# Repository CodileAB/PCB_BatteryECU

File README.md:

Wolley Battery ECU
==================

This is the KiCad project for the Wolley Battery ECU.

Specifications
--------------

| Name                       | Value          |
| -------------------------- | -------------- |
| PCB layers                 | 2              |
| PCB width                  | 103.20 mm      |
| PCB height                 | 117.00 mm      |
| Mount hole diameter        | 3.20 mm        |
| Bus voltage                | 5 V            |
| Max current                | 5 A            |
| Number of cells            | 10             |
| Cell type                  | Ni-MH (AA)     |
| Integrated charging        | Yes            |

Key Components
--------------

| Component | Part | Details |
| --------- | ---- | ------- |
| MCU | Infineon XMC1404_F064X200A | ARM Cortex-M0, 32-bit, 48 MHz, 200 kB flash |
| Step-down voltage regulator | TI LM22679TJ-5.0 | 42 V to 5 V switching regulator, 5 A |
| CAN transceiver | Infineon TLE7251VSJ | |
| Current sensor | MPS MCS1803GS-05P | Hall effect current sensor, 5 A |
| Temperature sensor | TI LM35DM | Precision centigrade temperature sensor |
| Battery charger | Maxim MAX1640 | Adjustable-output, switch-mode current sources with synchronous rectifier |

Licence
-------

Licenced under the CERN Open Hardware Licence v1.2.

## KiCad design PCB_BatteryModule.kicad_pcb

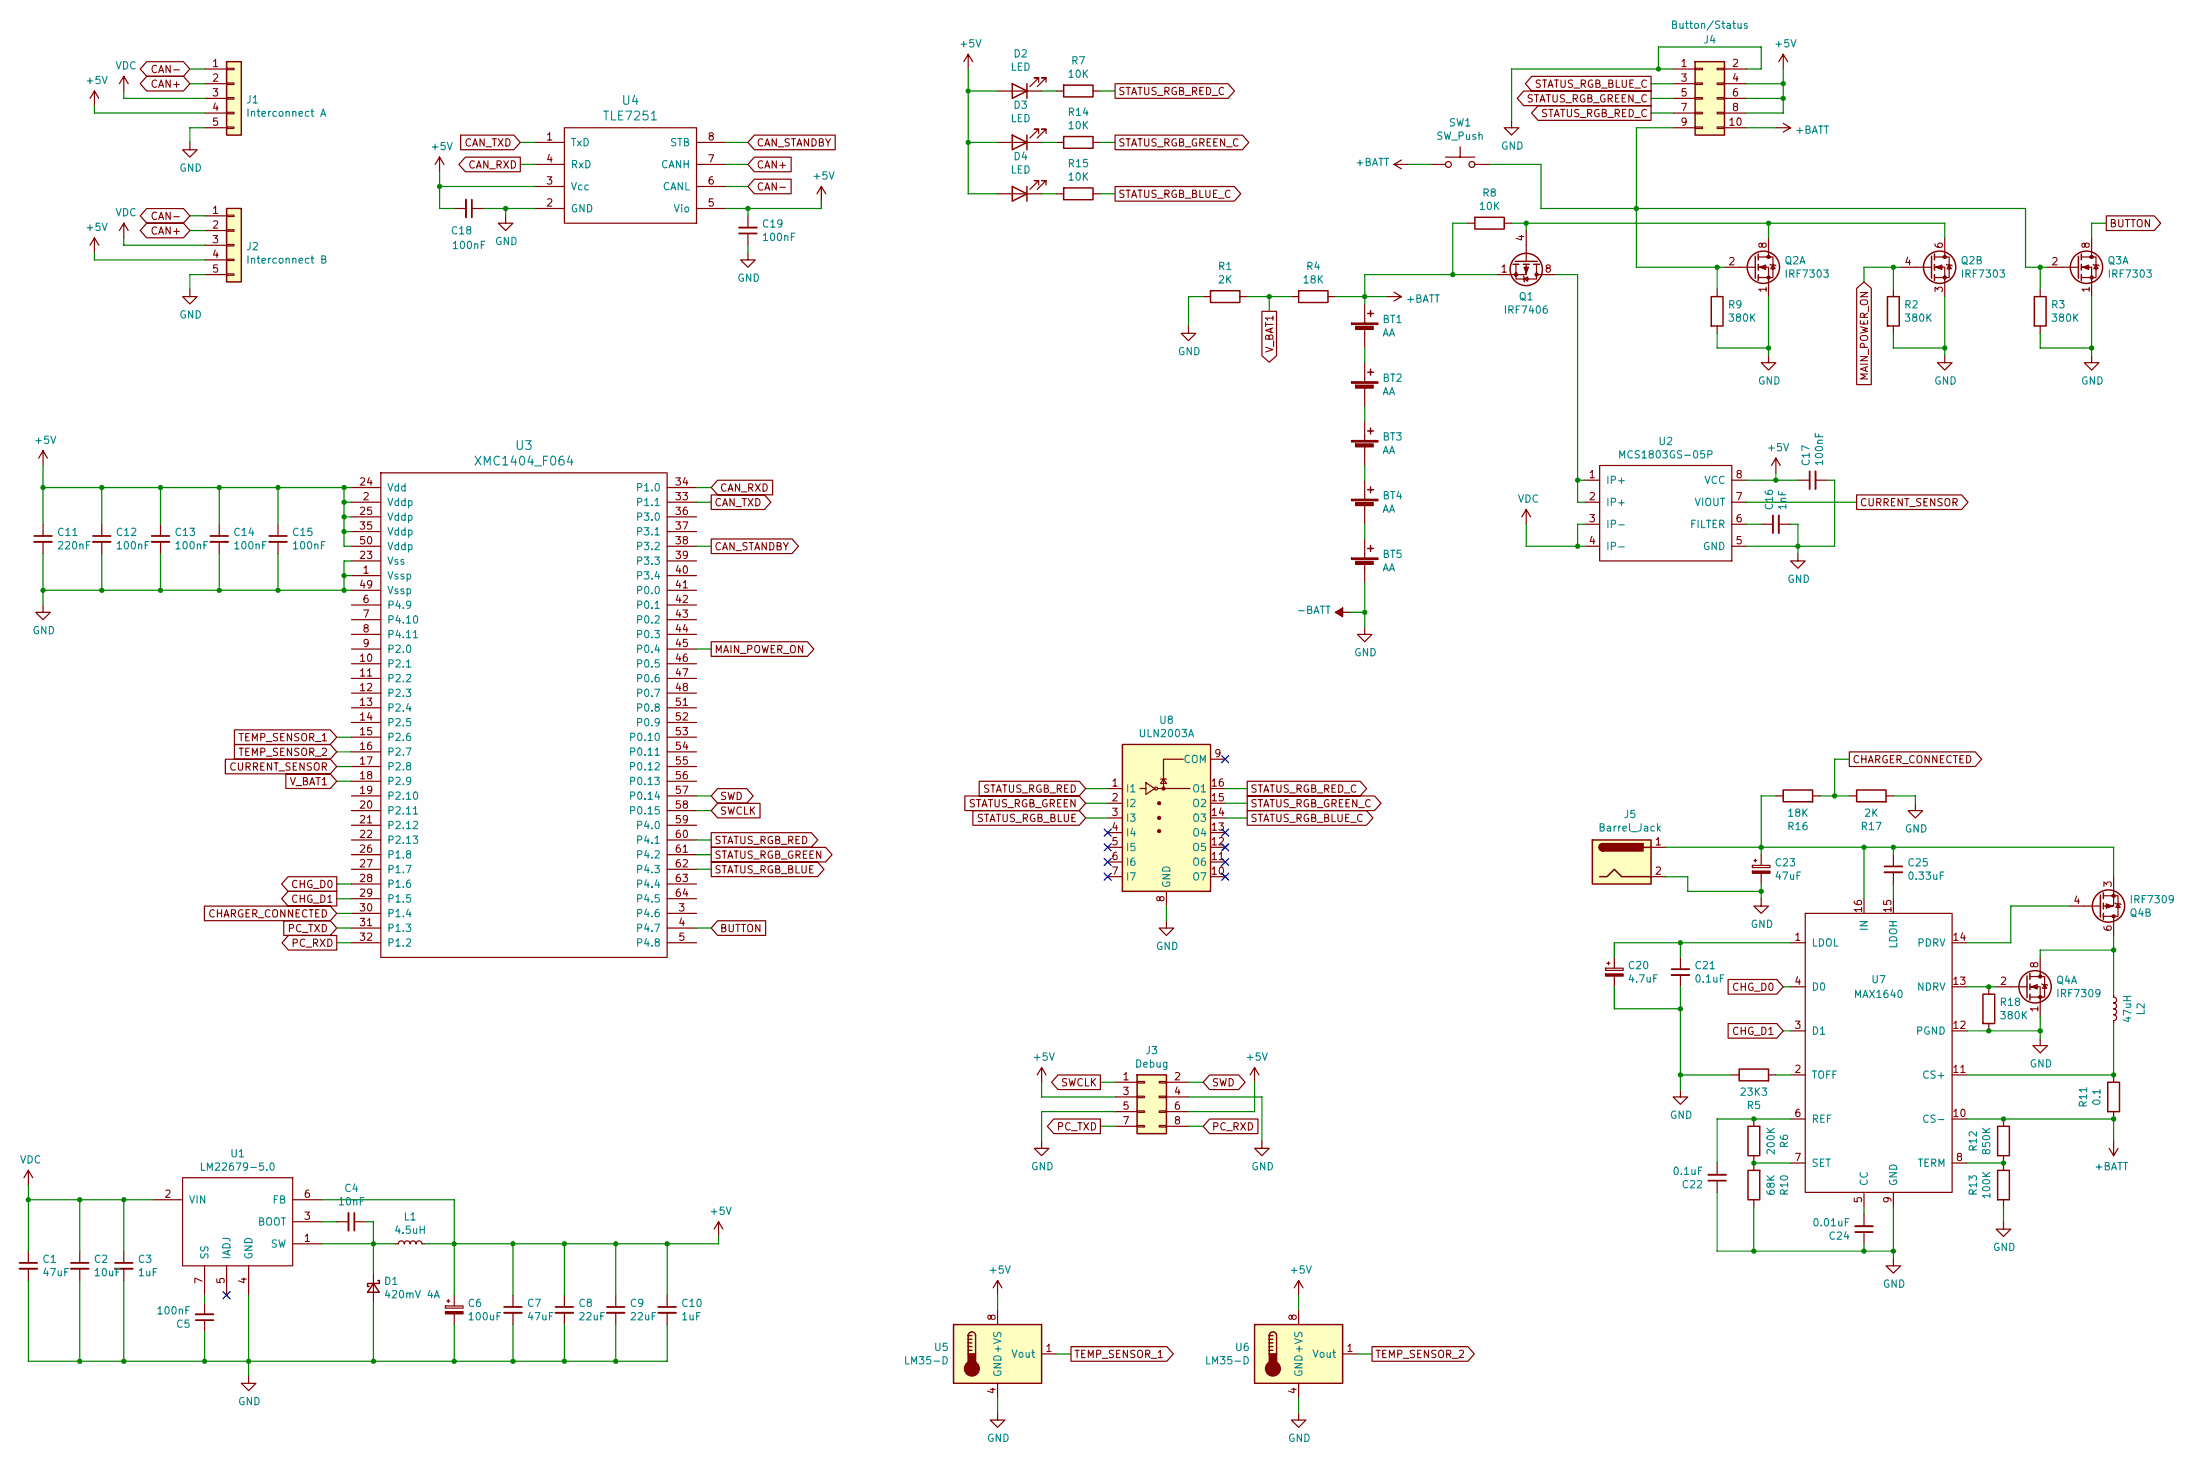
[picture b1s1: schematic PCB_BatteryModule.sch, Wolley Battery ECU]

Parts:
BT1, BT2, BT3, BT4, BT5: AA; Battery_AA_THT_Keystone_590
C1, C7: 47uF; C_0805_HandSoldering
C2: 10uF; C_0805_HandSoldering
C3, C10: 1uF; C_0805_HandSoldering
C4: 10nF; C_0805_HandSoldering
C5, C12, C13, C14, C15, C17, C18, C19: 100nF; C_0805_HandSoldering
C6: 100uF; CP_EIA-7343-43_Kemet-X_Pad2.25x2.55mm_HandSolder
C8, C9: 22uF; C_0805_HandSoldering
C11: 220nF; C_0805_HandSoldering
C16: 1nF; C_0805_HandSoldering
C20: 4.7uF; C_0805_HandSoldering
C21, C22: 0.1uF; C_0805_HandSoldering
C23: 47uF; CP_EIA-7343-43_Kemet-X_Pad2.25x2.55mm_HandSolder
C24: 0.01uF; C_0805_HandSoldering
C25: 0.33uF; C_0805_HandSoldering
D1: 420mV 4A; D_SMC
D2, D3, D4: LED; LED_0805_2012Metric_Pad1.15x1.40mm_HandSolder
J1: Interconnect A; WolletInterconnect_THT_Angeled
J2: Interconnect B; WolletInterconnect_THT_Angeled
J3: Debug; Pin_Header_Straight_2x04_Pitch2.54mm_SMD
J4: Button/Status; PinHeader_2x05_P2.54mm_Horizontal
J5: Barrel_Jack; BarrelJack_CUI_PJ-036AH-SMT_Horizontal
L1: 4.5uH; Inductor_SMD_Bourns_SRR1280
L2: 47uH; Inductor_SMD_Bourns_SRR1280
Q1: IRF7406; SOIC-8_3.9x4.9mm_P1.27mm
Q2, Q3: IRF7303; SOIC-8_3.9x4.9mm_P1.27mm
Q4: IRF7309; SOIC-8_3.9x4.9mm_P1.27mm
R1, R17: 2K; C_0805_HandSoldering
R2, R3, R9, R18: 380K; C_0805_HandSoldering
R4, R16: 18K; C_0805_HandSoldering
R5: 23K3; C_0805_HandSoldering
R6: 200K; C_0805_HandSoldering
R7, R8, R14, R15: 10K; C_0805_HandSoldering
R10: 68K; C_0805_HandSoldering
R11: 0.1; C_2010_5025Metric_HandSoldering
R12: 850K; C_0805_HandSoldering
R13: 100K; C_0805_HandSoldering
SW1: SW_Push; CK_Switch_KSC_Series
U1: LM22679-5.0; TO-263-7_TabPin8
U2: MCS1803GS-05P; SOIC-8_3.9x4.9mm_P1.27mm
U3: XMC1404_F064; TQFP-64_10x10mm_Pitch0.5mm_Handsoldering
U4: TLE7251; Infineon_PG-DSO-8-43
U5, U6: LM35-D; SOIC-8_3.9x4.9mm_P1.27mm
U7: MAX1640; QSOP-16_3.9x4.9mm_P0.635mm
U8: ULN2003A; SOIC-16_3.9x9.9mm_P1.27mm

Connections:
+5V: C6.1, C7.1, C8.1, C9.1, C10.1, C11.1, C12.1, C13.1, C14.1, C15.1, C17.1, C18.2, C19.2, D2.2 (A), D3.2 (A), D4.2 (A), J1.4, J2.4, J3.3, J3.6, J4.4, J4.6, J4.8, L1.2, U1.6 (FB), U2.8 (VCC), U3.2 (Vddp), U3.24 (Vdd), U3.25 (Vddp), U3.35 (Vddp), U3.50 (Vddp), U4.3 (Vcc), U4.5 (Vio), U5.8 (+VS), U6.8 (+VS)
+BATT: BT1.1 (+), J4.10, Q1.1 (S), Q1.2 (S), Q1.3 (S), R4.1, R8.2, R11.2, R12.1, SW1.1, U7.10 (CS-)
-BATT: BT5.2 (-), C1.2, C2.2, C3.2, C5.1, C6.2, C7.2, C8.2, C9.2, C10.2, C11.2, C12.2, C13.2, C14.2, C15.2, C16.2, C17.2, C18.1, C19.1, C20.2, C21.2, C22.1, C23.2, C24.1, D1.2 (A), J1.5, J2.5, J3.4, J3.5, J4.1, J4.2, J5.2, Q2.1 (S), Q2.3 (1), Q3.1 (S), Q4.1 (S), R1.2, R2.2, R3.2, R5.1, R9.2, R10.1, R13.2, R17.2, R18.2, U1.4 (GND), U2.5 (GND), U3.1 (Vssp), U3.23 (Vss), U3.49 (Vssp), U4.2 (GND), U5.4 (GND), U6.4 (GND), U7.9 (GND), U7.12 (PGND), U8.8 (GND)
BUTTON: Q3.7 (D), Q3.8 (D), U3.4 (P4.7)
CAN+: J1.2, J2.2, U4.7 (CANH)
CAN-: J1.1, J2.1, U4.6 (CANL)
CAN_RXD: U3.34 (P1.0), U4.4 (RxD)
CAN_STANDBY: U3.38 (P3.2), U4.8 (STB)
CAN_TXD: U3.33 (P1.1), U4.1 (TxD)
CHARGER_CONNECTED: R16.2, R17.1, U3.30 (P1.4)
CHG_D0: U3.28 (P1.6), U7.4 (D0)
CHG_D1: U3.29 (P1.5), U7.3 (D1)
CURRENT_SENSOR: U2.7 (VIOUT), U3.17 (P2.8)
MAIN_POWER_ON: Q2.4 (G), R2.1, U3.45 (P0.4)
unnamed: BT1.2 (-), BT2.1 (+)
unnamed: BT2.2 (-), BT3.1 (+)
unnamed: BT3.2 (-), BT4.1 (+)
unnamed: BT4.2 (-), BT5.1 (+)
unnamed: C4.1, D1.1 (K), L1.1, U1.1 (SW)
unnamed: C4.2, U1.3 (BOOT)
unnamed: C5.2, U1.7 (SS)
unnamed: C16.1, U2.6 (FILTER)
unnamed: C20.1, C21.1, U7.1 (LDOL)
unnamed: C22.2, R6.2, U7.6 (REF)
unnamed: C23.1, C25.1, J5.1, Q4.3 (1), R16.1, U7.16 (IN)
unnamed: C24.2, U7.5 (CC)
unnamed: C25.2, U7.15 (LDOH)
unnamed: D2.1 (K), R7.2
unnamed: D3.1 (K), R14.2
unnamed: D4.1 (K), R15.2
unnamed: J4.9, Q2.2 (G), Q3.2 (G), R3.1, R9.1, SW1.2
unnamed: L2.1, Q4.5 (D), Q4.6 (D), Q4.7 (D), Q4.8 (D)
unnamed: L2.2, R11.1, U7.11 (CS+)
unnamed: Q1.4 (G), Q2.5 (D), Q2.6 (D), Q2.7 (D), Q2.8 (D), R8.1
unnamed: Q1.5 (D), Q1.6 (D), Q1.7 (D), Q1.8 (D), U2.1 (IP+), U2.2 (IP+)
unnamed: Q4.2 (G), R18.1, U7.13 (NDRV)
unnamed: Q4.4 (G), U7.14 (PDRV)
unnamed: R5.2, U7.2 (TOFF)
unnamed: R6.1, R10.2, U7.7 (SET)
unnamed: R12.2, R13.1, U7.8 (TERM)
PC_RXD: J3.8, U3.32 (P1.2)
PC_TXD: J3.7, U3.31 (P1.3)
STATUS_RGB_BLUE: U3.62 (P4.3), U8.3 (I3)
STATUS_RGB_BLUE_C: J4.3, R15.1, U8.14 (O3)
STATUS_RGB_GREEN: U3.61 (P4.2), U8.2 (I2)
STATUS_RGB_GREEN_C: J4.5, R14.1, U8.15 (O2)
STATUS_RGB_RED: U3.60 (P4.1), U8.1 (I1)
STATUS_RGB_RED_C: J4.7, R7.1, U8.16 (O1)
SWCLK: J3.1, U3.58 (P0.15)
SWD: J3.2, U3.57 (P0.14)
TEMP_SENSOR_1: U3.15 (P2.6), U5.1 (Vout)
TEMP_SENSOR_2: U3.16 (P2.7), U6.1 (Vout)
VDC: C1.1, C2.1, C3.1, J1.3, J2.3, U1.2 (VIN), U2.3 (IP-), U2.4 (IP-)
V_BAT1: R1.1, R4.2, U3.18 (P2.9)

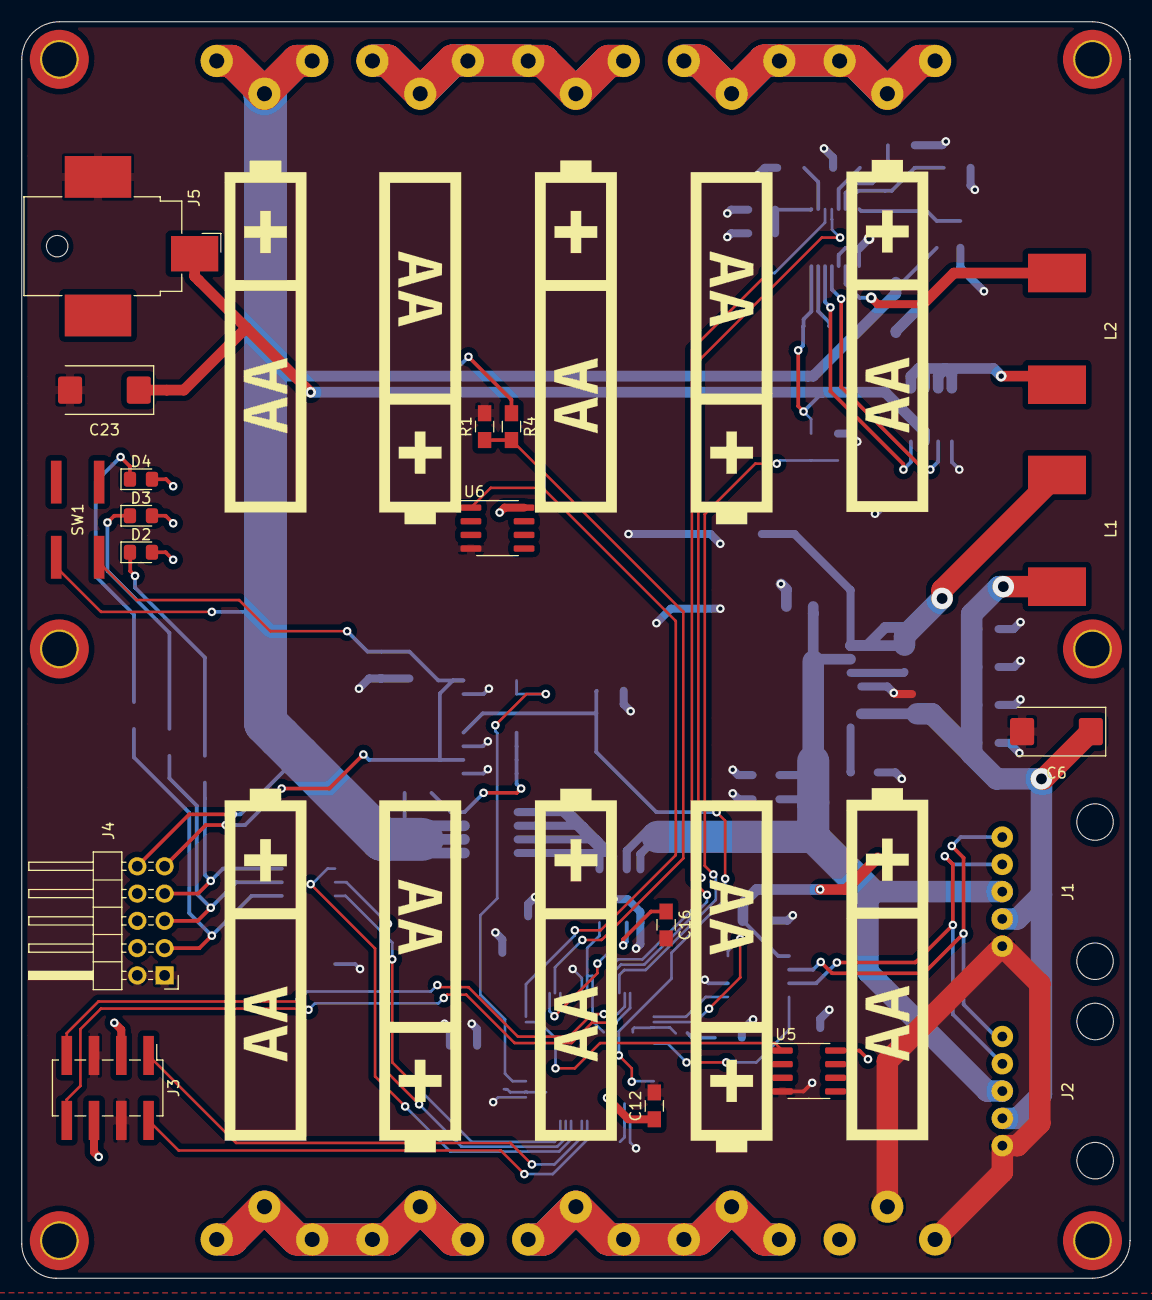
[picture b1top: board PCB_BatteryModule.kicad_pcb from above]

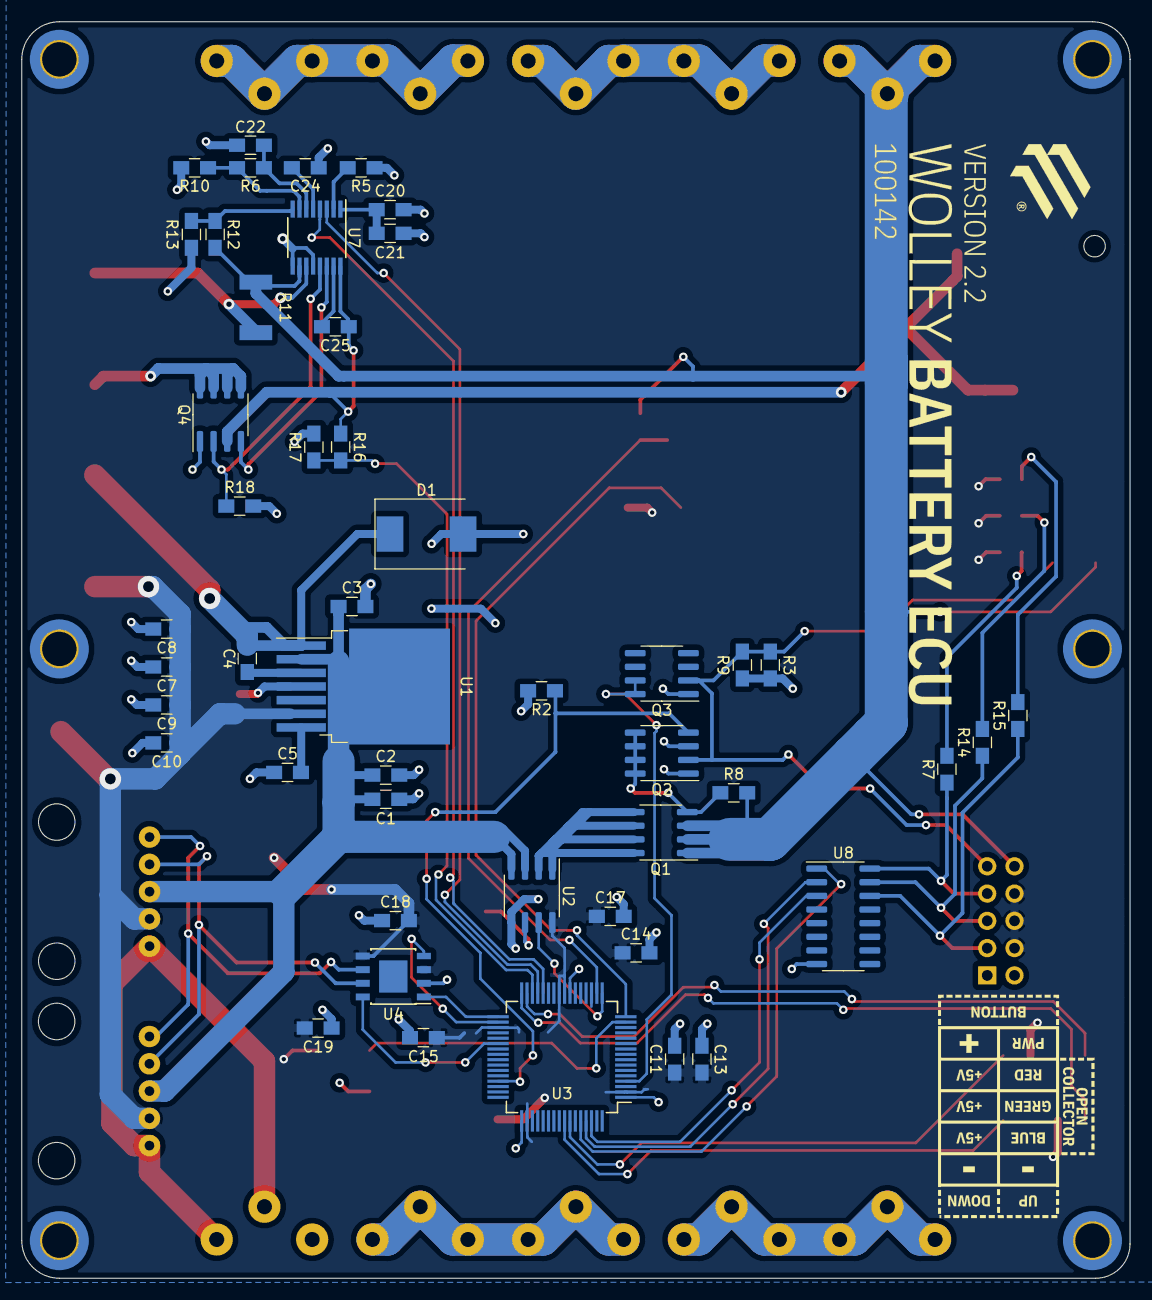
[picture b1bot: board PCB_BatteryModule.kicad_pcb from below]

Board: 2 copper layers, 103.2 x 117.0 mm, 72 parts (48 on the bottom side), 54 nets.

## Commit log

2021-10-28 Added files for version 1.0
2021-10-31 Add more info to the schematic and PCB
2021-10-31 Add README file
2021-10-31 Fix formatting in README
2021-11-06 Change the 0.1 uF capacitors to 100 nF which is the same
2021-11-06 Add the 5.0 suffix to the voltage regulator to make it more specific
2021-11-06 Bump the date
2022-08-17 Use AA Ni-Mh cells instead of 18650 Li-ion
2022-10-13 Version 2.0 with a lot of improvements
2022-10-19 Update the README
2022-11-25 Fix bug in the charger circuit where the P-channel mosfet was connected mirrored
2023-02-25 Update the version and part number text
2023-02-26 Update document data
2024-01-25 Add a pull-down resistor to the charger n-channel mosfet
    Adding a pull-down resistor to the gate of the n-channel mosfet
    prevents current from flowing through it when there is no charger voltage.
2024-01-27 Use the correct footprint for the button
2024-01-28 Change the D1 footprint to be regular SMC one instead of the handsoldering version
2024-02-18 Switch out the old logo to the new one and update the partnumber
2024-02-18 Update document revision etc.
2024-02-18 Commit the cache file
